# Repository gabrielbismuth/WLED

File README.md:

# WLED
This PCB is designed for W-LED control via GPIO pin 25. It includes reverse polarity protection to prevent damage from incorrect power connections. With a compact and efficient design, it integrates seamlessly into LED projects, ensuring reliable performance for both DIY and professional applications.

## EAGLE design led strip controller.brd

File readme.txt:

README - W-LED Control PCB

Overview

This PCB is designed for controlling W-LEDs with a dedicated GPIO control on pin 25. It features reverse polarity protection to prevent damage from incorrect power connections, ensuring safe and reliable operation.

Important Notice: Voltage Input Connection

When connecting the power input, be mindful of the terminal placement:

The PCB features a screw terminal for power input.

The polarity of the voltage applied on one terminal will be reflected on the corresponding side of the output terminal.

If you connect the positive voltage to the left terminal, the output terminal will also have the positive voltage on the left side.

If you connect the positive voltage to the right terminal, the output terminal will have the positive voltage on the right side.

Recommendation
Double-check your connections before powering the board.
Ensure correct polarity to avoid incorrect wiring in your setup.

Features
GPIO Control: Uses GPIO pin 25 for W-LED control.
Reverse Polarity Protection: Prevents damage from incorrect power connections.
Compact and Efficient Design: Ideal for various LED applications.
Applications
DIY LED lighting projects
Home automation

Professional LED installations

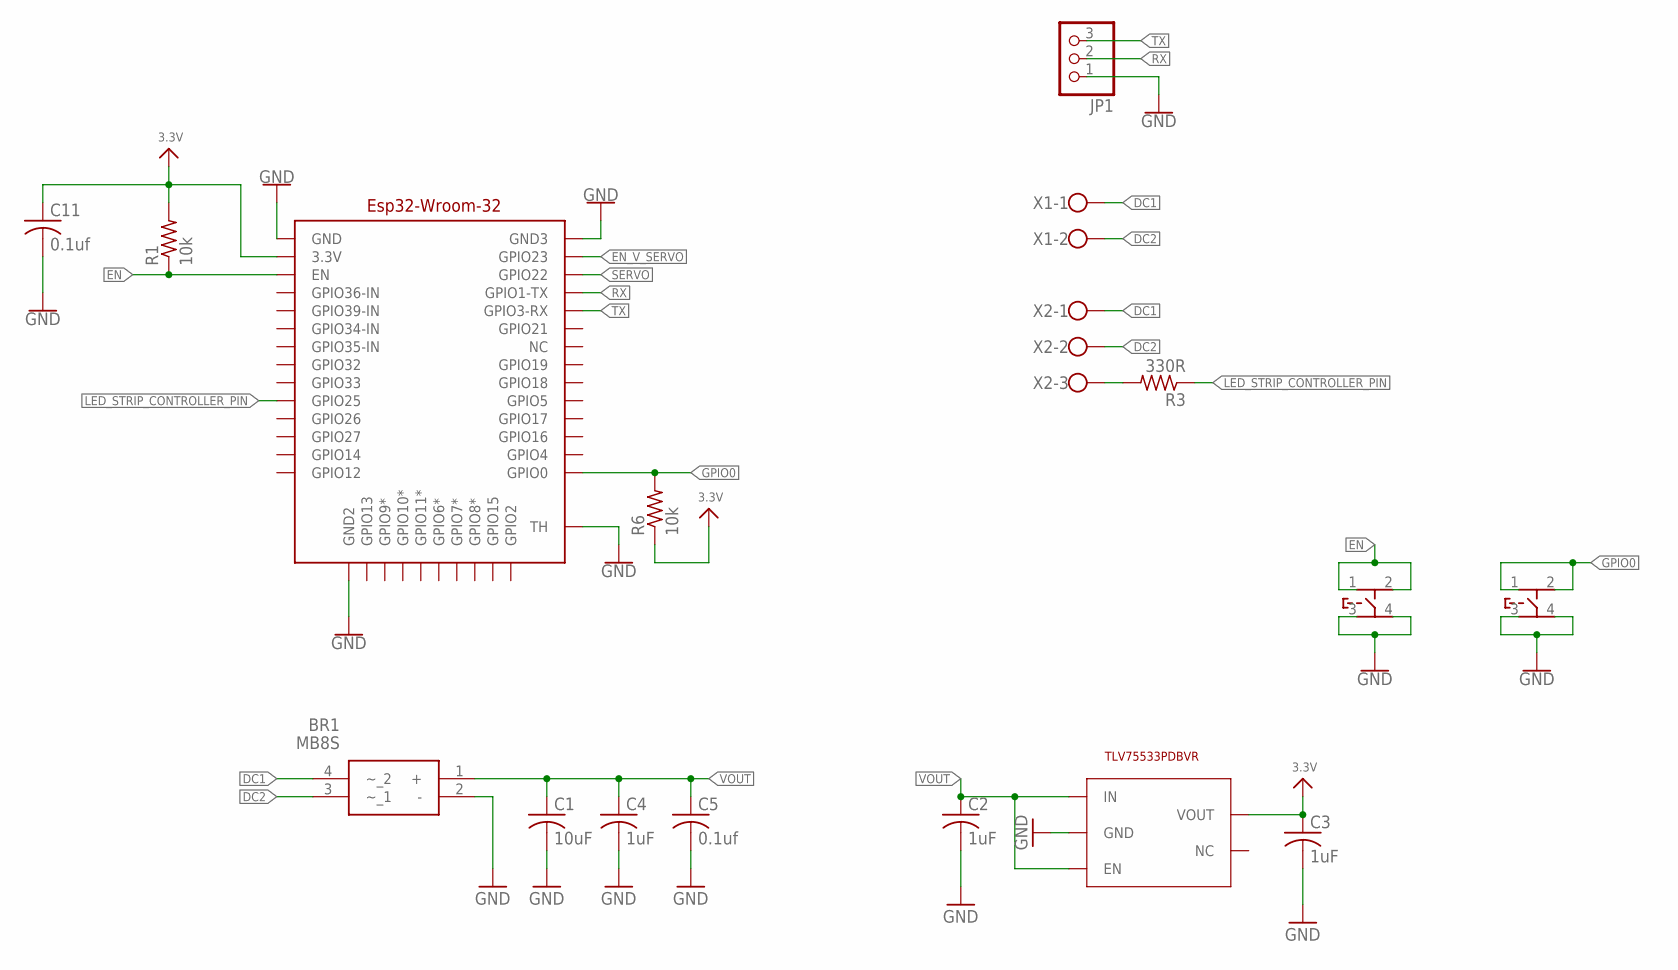
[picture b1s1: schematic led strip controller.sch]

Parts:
BR1: MB8S; SOP245P670X290-4N
C1: 10uF; C1206
C2, C3, C4: 1uF; C0603
C5, C11: 0.1uf; C0603
JP1: PINHD-1X3; 1X03
R1, R6: 10k; R0603
R3: 330R; R0603
U$1: ESP32-WROM-32; ESP-32FOOTPRINT
U$29: TLV75533PDBVR; SOT-23-5
U$33, U$34: XUNPU; TS-1089S
X1: W237-102
X2: W237-103

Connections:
3.3V: C3.1, C11.1, R1.2, R6.1, U$1.3.3V, U$29.VOUT
DC1: BR1.4 (~_2), X1.1, X2.1
DC2: BR1.3 (~_1), X1.2, X2.2
EN: R1.1, U$1.EN, U$33.1, U$33.2
EN_V_SERVO: U$1.GPIO23
GND: BR1.2 (-), C1.2, C2.2, C3.2, C4.2, C5.2, C11.2, JP1.1, U$1.GND, U$1.GND2, U$1.GND3, U$1.TH, U$29.GND, U$33.3, U$33.4, U$34.3, U$34.4
GPIO0: R6.2, U$1.GPIO0, U$34.1, U$34.2
LED_STRIP_CONTROLLER_PIN: R3.1, U$1.GPIO25
unnamed: R3.2, X2.3
RX: JP1.2, U$1.GPIO1 (GPIO1-TX)
SERVO: U$1.GPO22 (GPIO22)
TX: JP1.3, U$1.GPIO3 (GPIO3-RX)
VOUT: BR1.1 (+), C1.1, C2.1, C4.1, C5.1, U$29.EN, U$29.IN

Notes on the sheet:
TLV75533PDBVR

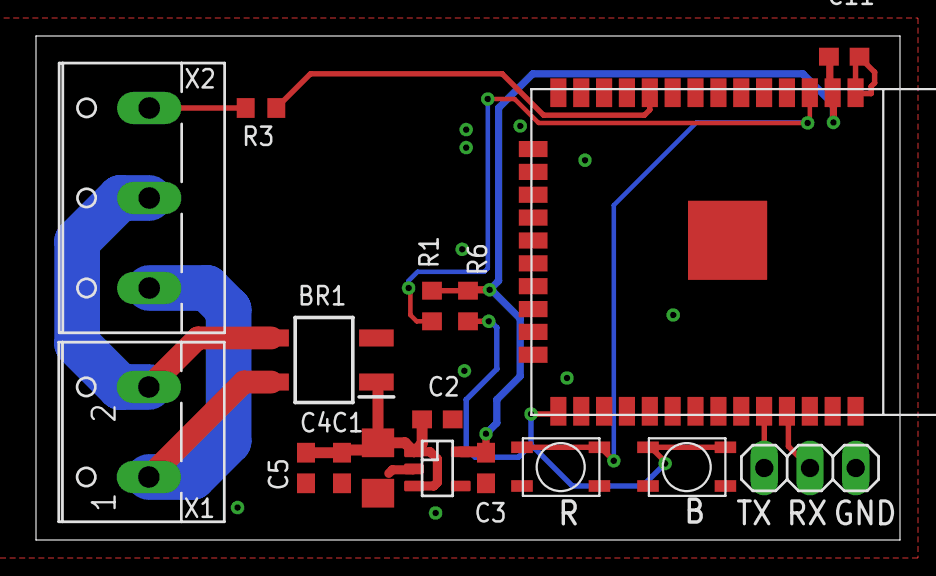
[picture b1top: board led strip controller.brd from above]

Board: 2 copper layers, 48.0 x 28.0 mm, 17 parts (0 on the bottom side), 11 nets.

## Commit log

2025-02-10 Add files via upload
    README - W-LED Control PCB
    Overview
    This PCB is designed for controlling W-LEDs with a dedicated GPIO control on pin 25. It features reverse polarity protection to prevent damage from incorrect power connections, ensuring safe and reli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
    Important Notice: Voltage Input Connection
    When connecting the power input, be mindful of the terminal placement:
    The PCB features a screw terminal for power input.

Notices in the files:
parts and their libraries:
SparkFun-PowerSymbols: Licensing: Creative Commons ShareAlike 4.0 International - https://creativecommons.org/licenses/by-sa/4.0
